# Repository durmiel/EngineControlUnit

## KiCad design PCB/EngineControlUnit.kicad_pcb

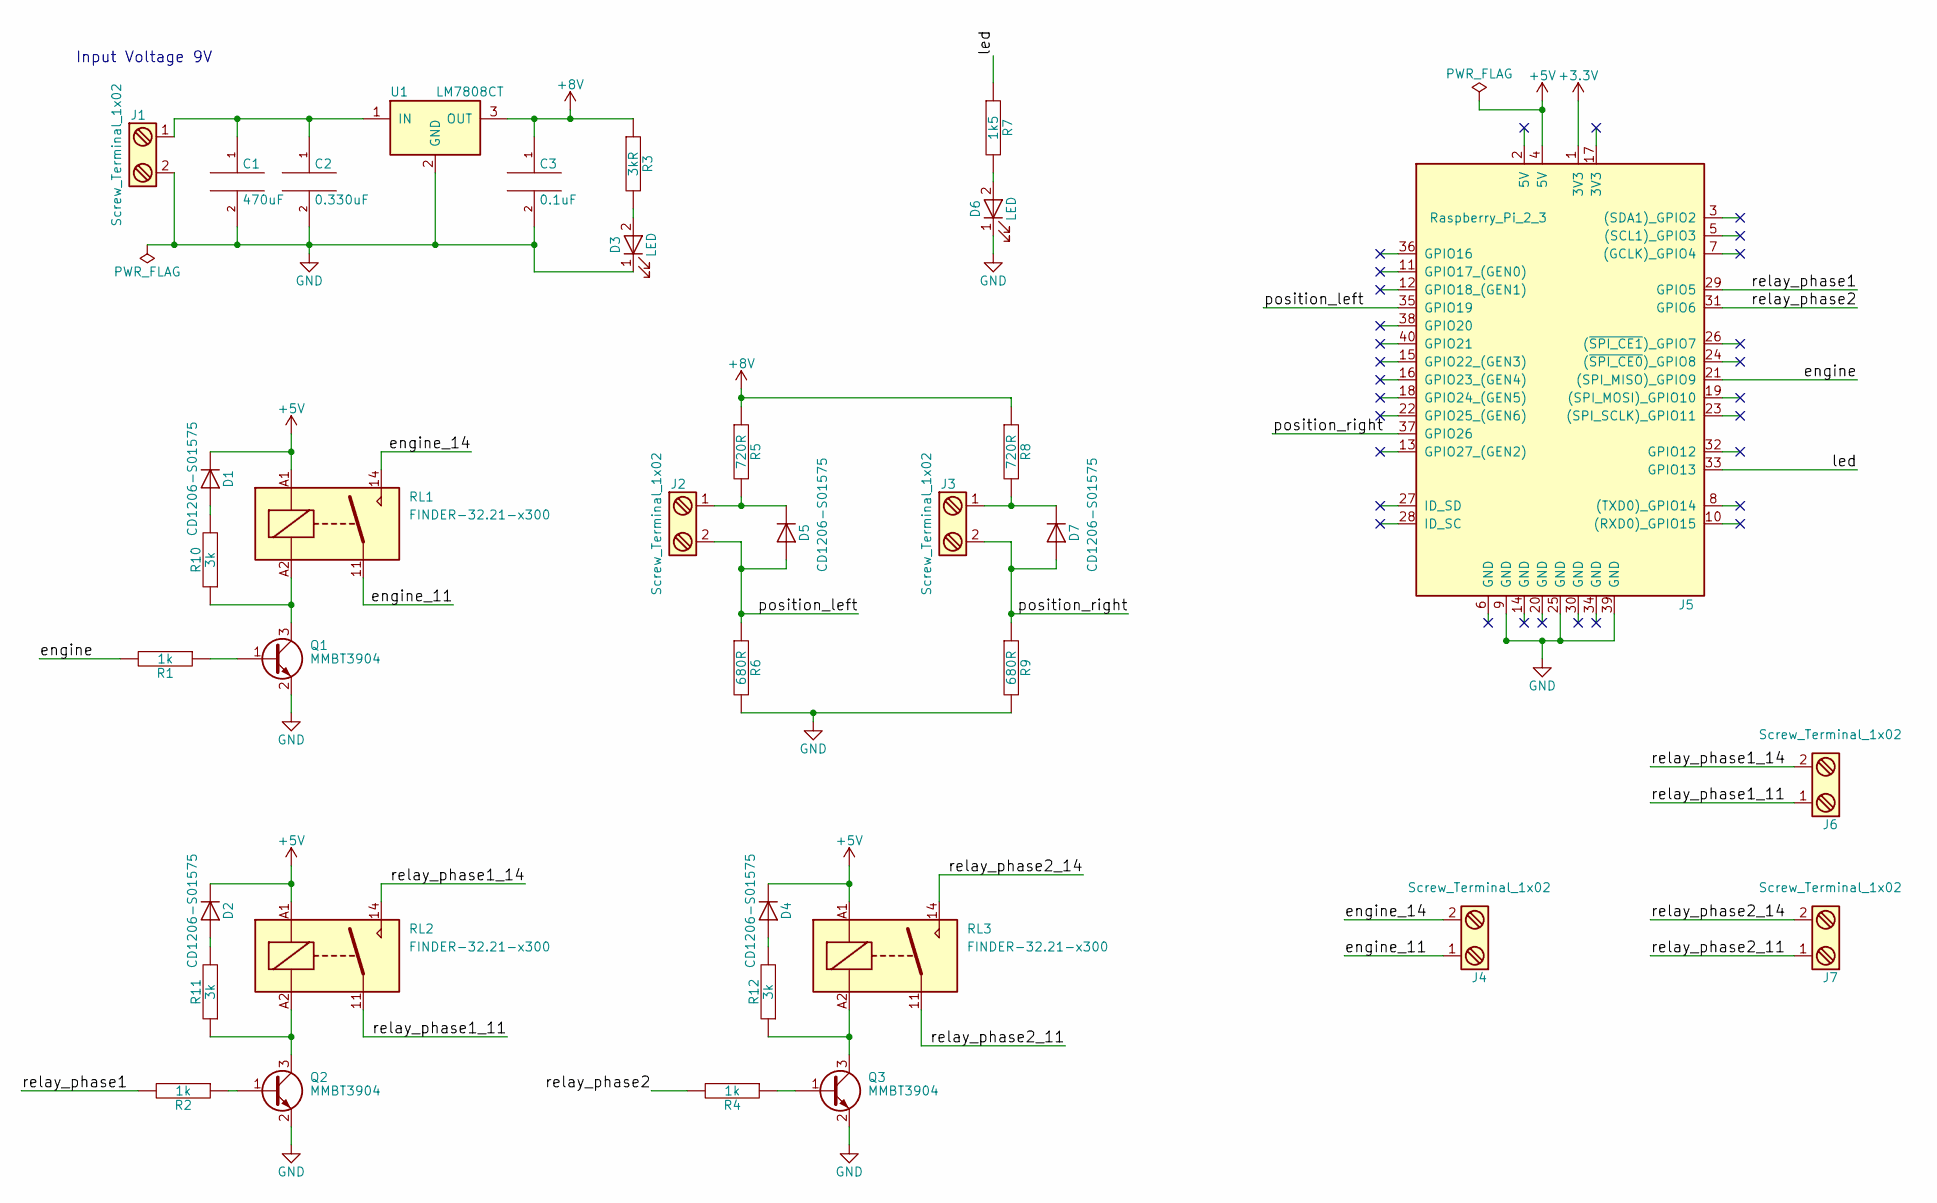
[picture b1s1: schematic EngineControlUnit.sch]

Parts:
C1: 470uF; C_1206_HandSoldering
C2: 0.330uF; C_1206_HandSoldering
C3: 0.1uF; C_1206_HandSoldering
D1, D2, D4, D5, D7: CD1206-S01575; D_1206
D3, D6: LED; D_1206
J1, J2, J3, J4, J6, J7: Screw_Terminal_1x02; bornier2
J5: Raspberry_Pi_2_3; Pin_Header_Straight_2x20_Pitch2.54mm
Q1, Q2, Q3: MMBT3904; SOT-23
R1, R2, R4: 1k; R_1206_HandSoldering
R3: 3kR; R_1206_HandSoldering
R5, R8: 720R; R_1206_HandSoldering
R6, R9: 680R; R_1206_HandSoldering
R7: 1k5; R_1206_HandSoldering
R10, R11, R12: 3k; R_1206_HandSoldering
RL1, RL2, RL3: FINDER-32.21-x300; Relay_SPDT_Finder_32.21-x000
U1: LM7808CT; TO-220_Vertical

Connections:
+5V: D1.1 (K), D2.1 (K), D4.1 (K), J5.4 (5V), RL1.A1, RL2.A1, RL3.A1
+8V: C3.1, R3.1, R5.1, R8.1, U1.3 (OUT)
/engine: J5.21 ((SPI_MISO)_GPIO9), R1.2
/engine_11: J4.1, RL1.11
/engine_14: J4.2, RL1.14
/led: J5.33 (GPIO13), R7.1
/position_left: D5.2 (A), J2.2, J5.35 (GPIO19), R6.1
/position_right: D7.2 (A), J3.2, J5.37 (GPIO26), R9.1
/relay_phase1: J5.29 (GPIO5), R2.2
/relay_phase1_11: J6.1, RL2.11
/relay_phase1_14: J6.2, RL2.14
/relay_phase2: J5.31 (GPIO6), R4.2
/relay_phase2_11: J7.1, RL3.11
/relay_phase2_14: J7.2, RL3.14
GND: C1.2, C2.2, C3.2, D3.1 (K), D6.1 (K), J1.2, J5.9 (GND), J5.25 (GND), J5.39 (GND), Q1.2 (E), Q2.2 (E), Q3.2 (E), R6.2, R9.2, U1.2 (GND)
unnamed: C1.1, C2.1, J1.1, U1.1 (IN)
unnamed: D1.2 (A), R10.2
unnamed: D2.2 (A), R11.2
unnamed: D3.2 (A), R3.2
unnamed: D4.2 (A), R12.2
unnamed: D5.1 (K), J2.1, R5.2
unnamed: D6.2 (A), R7.2
unnamed: D7.1 (K), J3.1, R8.2
unnamed: Q1.1 (B), R1.1
unnamed: Q1.3 (C), R10.1, RL1.A2
unnamed: Q2.1 (B), R2.1
unnamed: Q2.3 (C), R11.1, RL2.A2
unnamed: Q3.1 (B), R4.1
unnamed: Q3.3 (C), R12.1, RL3.A2

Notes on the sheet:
Input Voltage 9V

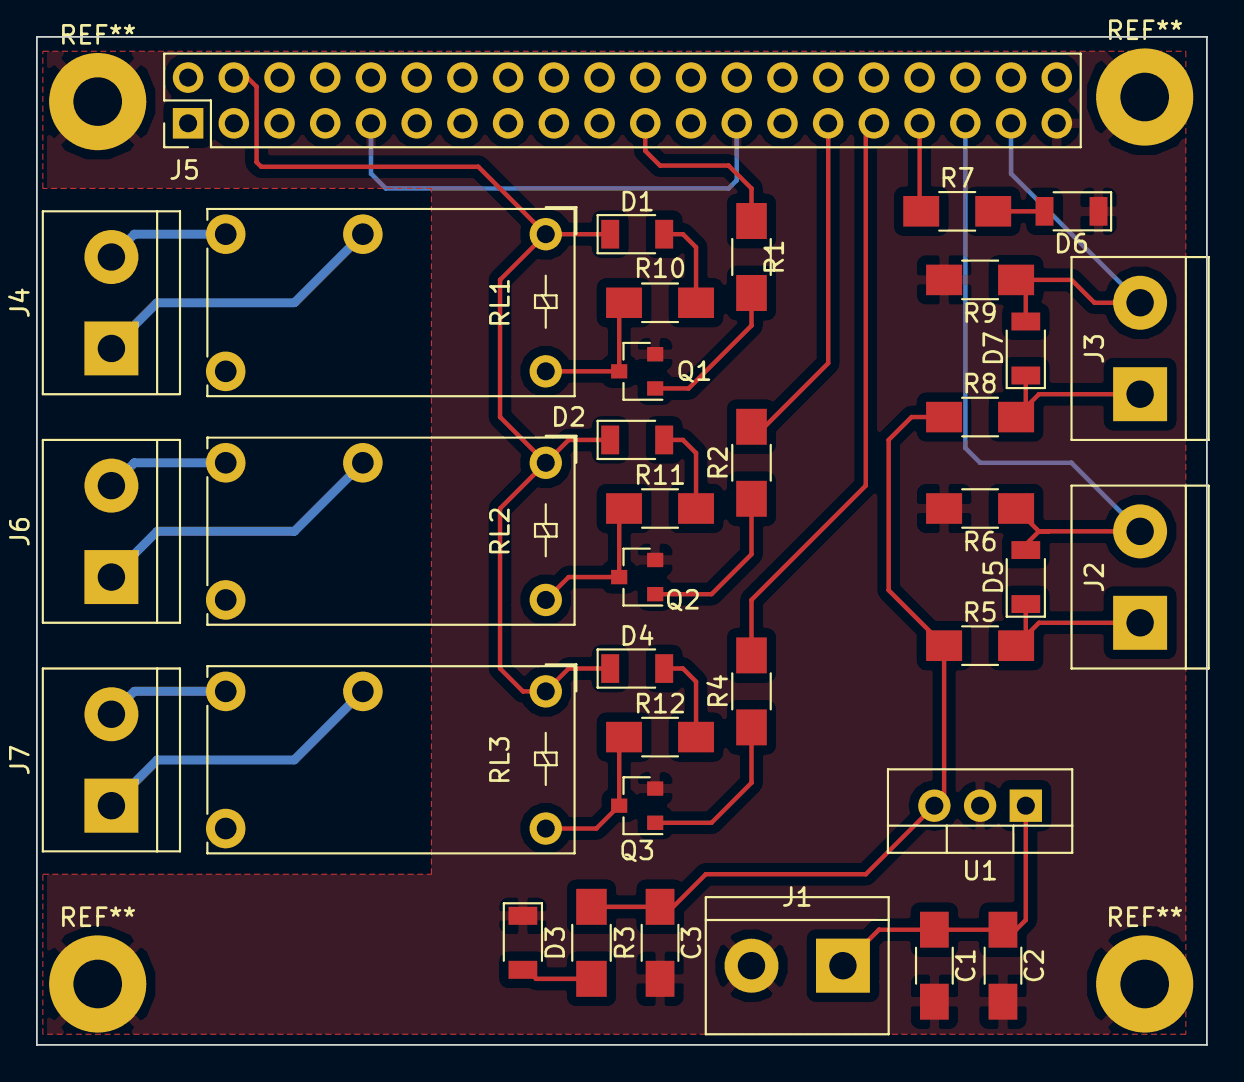
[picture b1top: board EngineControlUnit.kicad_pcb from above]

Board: 2 copper layers, 65.0 x 56.0 mm, 36 parts (0 on the bottom side), 29 nets.

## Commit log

2018-04-25 initial commit with the PCB files of the project
2018-04-25 add software to the project
